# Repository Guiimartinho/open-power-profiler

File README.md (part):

# Open Power Profiler

[![Checks: run on demand][badge-checks]](CONTRIBUTING.md#quality-gates)
[![Status: early development][badge-status]](#roadmap)
[![Software license: MIT][badge-mit]](LICENSE)
[![Hardware license: CERN-OHL-P v2][badge-ohl]](hardware/LICENSE)

Open-source power profiler in the class of the Nordic PPK2, built around the
Raspberry Pi Pico 2. It is designed to sample current at 100 kSPS from
100 nA to 1 A with automatic range switching, to work either as a source
meter that powers the device under test or as an ampere meter in series
with an external supply, and to stream the samples to a PC over USB.

The instrument is two boards: a Raspberry Pi Pico 2, bought ready-made,
plugged into a carrier board designed in this project that holds the
measurement electronics.

The picture is a rendering from the KiCad files of draft A2, with the
Pico 2 on its sockets. It is not a photograph: no board has been built.

> [!NOTE]
> The project is in early development. No hardware has been built and
> nothing has been measured. The performance figures in this repository
> are design targets, the circuits of the board are simulated from its
> netlist, and the figures of the board are calculated from the drawn
> copper. [Project Status](#project-status) says what exists, what it
> rests on and what comes next.

## Table of Contents

- [Project Status](#project-status)
- [Target Specifications](#target-specifications)
- [How It Works](#how-it-works)
- [Connections](#connections)
- [Hardware Draft](#hardware-draft)
- [Circuit Simulations](#circuit-simulations)
- [Repository Structure](#repository-structure)
- [Roadmap](#roadmap)
- [Getting Started](#getting-started)
- [Engineering Practices](#engineering-practices)
- [Documentation](#documentation)
- [Contributing](#contributing)
- [License](#license)
- [Acknowledgments](#acknowledgments)

## Project Status

As of 2026-10-13. Draft A2 of the carrier board is the present state of
the hardware: the whole schematic, a specification written for it, and a
board with every part placed and every one of its 984 connections drawn.
The board was first routed by an autorouter, which left 28 connections
open. Its layout has since been reviewed: the open connections are closed
and the copper that an autorouter does not draw is drawn, the pours of the
1 A path, the guard, the sense pairs and the copper of the converters. The
review was done with scripts and checked by independent calculation. The
seven points where the reviewed board departs from the first wording of
section 10 of the specification are recorded decisions, D-87 to D-93, and
the specification follows them.

On 2026-10-13 a person looked at the drawings for the first time: the
project owner opened the schematic and the board in the KiCad editor and
found both coherent. It was a look, not a review item by item, and no
edit was saved. The same day the footprints and the placement were
reviewed on a copy of the project, with scripts on the board file, 3D
renderings of every region of the board and the datasheets. Five findings
of that review were worked into the board at single points, with no new
routing, and the silkscreen got the frames and names of the functional
blocks
([Review of Footprints and Placement](#review-of-footprints-and-placement)).
What is open is the review of the board item by item in the KiCad
editor, a list of items that need parts moved, what the silkscreen and
the test points still lack, and the thermal check of D-93.
Every figure of the board is calculated from the drawn copper, none is
measured; the package in [`tools/board/`](tools/board/README.md)
reproduces them from the board file.

Later on 2026-10-13 the project owner asked for the files that are needed
to send the board to fabrication. The fabrication outputs of draft A2 are
filed in
[`hardware/fabrication/draft-a2/`](hardware/fabrication/draft-a2/README.md)
for an order of proof-of-concept boards: eleven Gerber files of the
four-layer board, two drill files and two files for machine assembly.
That is decision D-105 of the specification. The items that the
specification puts before an order are still open, boards made from
these files are draft A2 and not revision A, and those items stay open.
No order is recorded: no board has been ordered or made as far as the
repository shows.

On 2026-10-10 the circuits of the schematic were simulated as well, block
by block, from its netlist: 134 benches in ngspice, of which 93 run
circuits of the board and 41 put the models into the test circuits of
their datasheets. The central design figures of the specification come
out again. The simulations raised four points for a decision before
boards are ordered, and the project owner decided them the same day: they
are decisions D-95 to D-98 of the specification. Three of them are drawn
since that day, as changes of values, part numbers and texts that move no
copper: 10 nF at three capacitors of the rail monitor (D-95), the two
parts of the damper on the module input fitted (D-98), and the text of
the detector position at the boost converter, which stays without a part
(D-97). The schematic, the board, the bill of materials and the netlist
snapshot of the simulations hold them, and the electrical rules check and
the design rules check report nothing on these files (run again on
2026-10-13).
The fourth is not drawn: a position for a capacitor at the buffer of the
driver rail (D-96), which needs a footprint and copper. The simulations
were not run again, so their results are still those of the circuit
before the three changes.

In fourteen places the simulations differed from a figure or a rule of
the specification or showed something that it did not state. The owner
asked for the text to follow the simulations: twelve places are corrected
in the specification, three of them by decisions D-99 to D-101, two wait
for the run of the benches on the drawn decisions, and seven questions
that the corrections leave are open, each with one recommendation. A
simulation is not a measurement: every active part in it is a model
written from a datasheet, a typical part at room temperature.
[Circuit Simulations](#circuit-simulations) shows the state.

The software is written ahead of the hardware and is tested without it.
Its state is that of 2026-10-12. On that day the firmware got a design of
its own, one level below the specification; the host protocol went to
version 2, which holds what draft A2 reports (D-103); and the firmware
directory became a project of the Pico SDK that builds an image for the
Pico 2. That image starts a console and the device state machine and
nothing more, and it has not been loaded onto a board: nothing has run on
a controller.

| Area | What exists | What is open |
| --- | --- | --- |
| [Specification](docs/specification.md) | The baseline of draft A2: requirements R-01 to R-17, analog and firmware design, pin map, host protocol, 105 recorded decisions and 36 firmware rules that guard hardware. D-95 to D-98 are the decisions of the project owner on the four points that the simulations raised, D-99 to D-101 are the three corrections of the text that change a rule, a test or advice to the user, and D-102 settles the license of the simulation folder. D-103 and D-104 are the decisions of 2026-10-12 on the software: version 2 of the host protocol, and the over-current trip as a program of its own in PIO 2. D-105 is the decision of 2026-10-13 on the first order: the fabrication outputs of draft A2 are filed for proof-of-concept boards while the items that precede an order are open | Every figure is a datasheet value, a calculation, a simulation or an estimate; the tests of its section 11 have to confirm them. The items of its section 16 under "Before the board is ordered" stay open after D-105 and remain conditions of revision A. Of the four decisions D-95 to D-98, three are drawn since 2026-10-10; the fourth, a position for a capacitor at the buffer of the driver rail (D-96), is stated here and not drawn. Of the fourteen other places where the simulations of 2026-10-10 differed from its text, twelve are corrected; two wait for the new run of the benches, and seven questions that the corrections leave are open in its section 16 |
| [Schematic](hardware/doc/README.md) | 428 parts on 15 pages. Three decisions that follow the simulations are drawn in it since 2026-10-10: 10 nF in place of 1 nF at three capacitors of the rail monitor (D-95), the two parts of the damper on the module input fitted (D-98), and the text of the detector position at the boost converter, which stays without a part (D-97). It passes the electrical rules check, run again on 2026-10-13. Before these three changes the netlist of the draft was checked independently against the datasheets, and its circuits were simulated from it. On 2026-10-13 its symbols were compared with the libraries and the datasheets: 55 of the 59 symbols of the parts are unchanged symbols of the KiCad library, and the four symbols of the project agree pin by pin with their datasheets. One field changed that day and no connection: the pre-regulator names a new project footprint | The [component checks](docs/checks/README.md): none is closed, so every part is a candidate; the comparison of 2026-10-13 closes none. One decision that follows the simulations is not drawn: a position for a capacitor at the buffer of the driver rail (D-96). The circuits that the three drawn changes touch have not been simulated again |
| [Board](hardware/README.md#board) | 150 mm × 100 mm, four layers, 425 footprints, 984 of 984 connections drawn, no violation in the design rules check, run again on 2026-10-13. The layout was reviewed on 2026-10-10 with scripts and checked by independent calculation. The three decisions drawn that day changed fields of six footprints (values, part numbers, fitted flags and one text) and no copper. On 2026-10-13 the project owner opened the project in the KiCad editor and found the schematic and the board coherent, and the footprints and the placement were reviewed with scripts on the board file, 3D renderings and the datasheets: every footprint equals its library footprint, no courtyard overlaps another, and nothing stands under the module. Five findings of that review are worked into the board: the pre-regulator stands on the land pattern of its own package, nine vias were moved away from pads and two from under the wall of the shield can, the reference texts stand at their own parts, and the console header has its pin names. The silkscreen carries the frames and names of the sixteen functional blocks. Calculated from the drawn copper, again after that round and unchanged: the 1 A path is 19.5 squares in source meter mode and 23.3 squares in ampere meter mode against a limit of 30, and the surface leakage into the measured node is 5.1 nA against a budget of 10 nA. The seven points where the layout departs from the first wording of section 10 of the specification are recorded as decisions D-87 to D-93 | No person has reviewed the board item by item in the KiCad editor: the owner's look of 2026-10-13 was not that review, and the review of footprints and placement was made outside the editor. Open items need parts moved, the capacitor loops of the converters among them. On the silkscreen 95 of the 425 reference texts are hidden, and the net names of the test points, the functions of the two jumpers and a frame for the serial number are missing; probe grounds at the test points are missing too. Two vias still stand at a pad, the lower edge of the frame of the shield can is not confirmed in a drawing of its maker, and the finger lands of the pre-regulator are not drawn. The temperature rise of the linear regulator is an open check, read on the first board (D-93). The position for a capacitor of D-96 is not on the board yet: it adds one footprint |
| [Bill of materials](hardware/doc/bom.csv) | 151 lines for 370 parts, each line with a part number and a maker, exported from the schematic on 2026-10-10 with the drawn decisions: the three capacitors of the rail monitor at 10 nF (D-95) and the two parts of the damper on the module input (D-98). Exported again on 2026-10-13: one line changed, the footprint of the pre-regulator | Three lines had no stock on 2026-10-09, among them the capacitor that the damper uses. One position stays without a part and is not in the file: the detector position at the boost converter (D-97) |
| [Fabrication outputs](hardware/fabrication/draft-a2/README.md) | Filed on 2026-10-13 for an order of proof-of-concept boards of draft A2, by decision D-105 of the project owner: eleven Gerber files of the four-layer board and two drill files, also as one archive, and two files for machine assembly with the 360 surface-mount placements of the top side in 142 lines. They were exported from the board file with `kicad-cli`. Two things were checked on them: the drill file holds 787 plated holes, which are the 694 vias and the 93 holes of pads of the board, and every layer, the drill file and the placement file lie in one coordinate frame | No order is recorded: no board has been ordered or made as far as the repository shows. No Gerber viewer has read the files back, and no manufacturer has reviewed them. The assembly files carry manufacturer part numbers only, and their rotations are those of KiCad. The order is the project owner's; it still needs the surface finish ENIG in the order form, a word on the mark of the order number, the rotations checked in the preview of the assembler, and the parts matched by their manufacturer part numbers. Boards made from these files are draft A2, not revision A |
| [Circuit simulations](simulation/README.md) | The circuits of draft A2 simulated in ngspice on 2026-10-10 from the netlist of the schematic as it stood that day, before the three decisions were drawn, in a package of their own (D-94): 134 benches, 93 on the circuits of the board in ten blocks and 41 that put the models written for the project into the test circuits of their datasheets. Of 3162 figures 1834 pass, 122 fail and 1206 carry no limit. The central design figures of the specification come out again block by block: shunt ladder, signal chain, range logic with requirement R-07, source meter, output stage, path switches, rails, power input and digital lines. The package has 777 tests; lines and branches are covered in full, the one module that loads the simulator excepted; its gates passed again on 2026-10-12 | The four points that the simulations raised are decided (D-95 to D-98): the capacitors of the rail monitor, the buffer of the driver rail, the detector position at the boost converter and the damper on the module input. Three of them are drawn since 2026-10-10 and are in the netlist snapshot of the package (D-95, D-97, D-98); the snapshot still matches the schematic on 2026-10-13. The results are still those of the run of 2026-10-10, on the circuit before these changes: the benches were not run again, and those of the power input still leave the two parts of the damper out. Open work: the benches brought in line with the snapshot, and the blocks that the changes touch run again, the rail monitor with the power-up and the power-off and the input from the module. In fourteen places the simulation and the text of the specification differed: twelve are corrected in the specification, two wait for the new run, and seven questions are open. The limits of the benches are still those of the earlier text. What stays for the bench: leakage at the nanoampere level, the multiplexer at +12 V and −4 V, the programs of the controller, coupling through the board, temperature. Every active part is a model written from its datasheet, and nothing is measured. The simulations ran on one machine; the `Simulation` workflow has not been started yet |
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
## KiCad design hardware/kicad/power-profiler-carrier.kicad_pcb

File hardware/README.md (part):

# Hardware

The carrier board of the instrument: schematic, PCB layout and fabrication
outputs. The simulations of its circuits are a package of their own, in
[`../simulation/`](../simulation/README.md).

The instrument is two boards. A Raspberry Pi Pico 2, bought ready-made, is
the controller. It plugs into two rows of pin sockets on the carrier board
designed here, which holds everything else: power input, source meter, shunt
ladder, signal chain, side data and connectors. Sections 4.11 and 5 of the
[specification](../docs/specification.md) define the interface.

The picture is a rendering from the KiCad files, with the Pico 2 on its
sockets. It is not a photograph: no board has been built.

## Status

Draft A2 with a reviewed layout, as of 2026-10-13. The KiCad project holds
the whole carrier board: the schematic with 428 parts on fifteen A4 pages
(the root sheet and fourteen sheets) and a four-layer board of
150 mm × 100 mm on which every connection is drawn. The board was placed by
a script and routed by an autorouter, which left 28 connections open. On
2026-10-10 its layout was reviewed with scripts: the open connections were
closed and the copper that an autorouter does not draw was drawn. Every
figure of the board in this guide is calculated from the drawn copper. On
the same day the circuits of the schematic were simulated from its netlist,
block by block; the central design figures of the specification come out
again ([Circuit Simulations](#circuit-simulations)). The simulations
raised four points, which the owner decided the same day: decisions D-95
to D-98 of the specification. Three of them are drawn since that day, as
changes of values, part numbers, fitted flags and texts: 10 nF at C32 to
C34 (D-95), the damper R14 and C5 fitted (D-98), and the text of the
position U9, which stays without a part (D-97). They changed no copper and
moved no part. The fourth is not drawn: a position for a capacitor at the
buffer U28 (D-96), which needs a footprint and copper. The simulations
were not run again, so their results describe the circuit before the
three changes
([Decisions That Follow the Simulations](#decisions-that-follow-the-simulations)).

On 2026-10-13 the owner opened the project in the KiCad editor, the
schematic and the board, and found both coherent. That was a look, not a
review item by item, and no edit was saved. The same day the footprints
and the placement were reviewed on a copy of the project, with scripts on
the board file, 3D renderings of every region of the board and the
datasheets. Five findings of that review were worked into the board, at
those points only and with no new routing: the pre-regulator U16 has the
land pattern of its own package, eleven vias were moved away from pads and
from under the wall of the shield can, reference texts stand at their own
parts, and the console header J1 has the names of its pins. The silkscreen
also carries the frames and names of the sixteen functional blocks now
([Review of Footprints and Placement](#review-of-footprints-and-placement-2026-10-13)).
Both rule checks report nothing on the present files (run on 2026-10-13).
Nobody has reviewed the board item by item in the KiCad editor, no board
is built, and nothing is measured.

Later that day the owner asked for the files that are needed to send the
board to fabrication. The fabrication outputs of draft A2 are filed in
[`fabrication/draft-a2/`](fabrication/draft-a2/README.md) for an order of
proof-of-concept boards. That is decision D-105 of the specification: the
items that the specification puts before an order are still open, boards
made from these files are draft A2 and not revision A, and those items
stay open
([Fabrication Outputs of Draft A2](#fabrication-outputs-of-draft-a2)).
No order is recorded: no board has been ordered or made as far as the
repository shows.

| What | State |
| --- | --- |
| Schematic | Every sheet drawn: 428 parts, 225 nets, 15 pages; not changed by the layout review. Three decisions of 2026-10-10 are drawn in it since that day, as changes of values, part numbers, fitted flags and texts: 10 nF at C32 to C34 (D-95), R14 and C5 fitted (D-98), the text of the position U9 (D-97). One is not drawn: the position for a capacitor at U28 (D-96). On 2026-10-13 one field changed and no connection: U16 on the Source Meter sheet, and its symbol in the project library, name the new project footprint |
| Electrical rules check | 0 errors, 0 warnings; run again on 2026-10-13, after the round that followed the review of footprints and placement |
| Netlist against datasheets | Checked independently, before the three decisions were drawn; no blocker and no major defect found |
| Symbols and footprints against libraries and datasheets | Compared on 2026-10-13: every footprint of the board equals its library footprint pad by pad, 55 of the 59 symbols of the parts are unchanged symbols of the KiCad library, and the four project symbols agree pin by pin with their datasheets ([list](#what-was-compared)). It closes no component check |
| Bill of materials | 151 lines for 370 parts, each line with a part number and a maker; three lines without stock on 2026-10-09; not changed by the layout review. Exported again on 2026-10-10: it holds 10 nF at C32 to C34 (D-95) and the two parts of the damper, R14 and C5 (D-98). Exported again on 2026-10-13: one line changed, the footprint of U16 |
| Component checks | 0 closed; every part is a candidate |
| Board, placement | 425 footprints placed by a script, all on the top side; 35 of them moved or turned in the layout review, none since. Reviewed on 2026-10-13 with scripts on the board file, 3D renderings and datasheets: no courtyard overlaps another, nothing stands under the module, 58 parts stand inside the shield can and none across its wall ([list](#what-was-compared)). Not reviewed item by item by a person in the KiCad editor |
| Board, routing | 984 of 984 connections, none open: 8.40 m of track in 3,743 segments, 694 vias, 42 copper zones. The round of 2026-10-13 routed nothing again: it moved eleven vias and added 27 short pieces of track, 15.9 mm in all, to the 3,716 segments that the board had (8.38 m), which are unchanged |
| Design rules check with schematic parity | 0 violations, 0 unconnected pads, 0 footprint errors, 0 differences between board and schematic, against a rule file that asks more than the one of the autorouted board; run again on 2026-10-13, after the round of that day |
| Layout review | Done on 2026-10-10 with scripts and checked by independent calculation |
| Look in the KiCad editor | On 2026-10-13 the owner opened the schematic and the board in the KiCad editor and found both coherent. A look, not a recorded review item by item; no edit was saved |
| Review of footprints and placement | Done on 2026-10-13 on a copy of the project, with scripts on the board file, 3D renderings of every region of the board and the datasheets. Five findings, each worked into the board the same day ([section](#review-of-footprints-and-placement-2026-10-13)) |
| Silkscreen | Since 2026-10-13: the frames and names of the sixteen functional blocks, the pin names of the console header J1, and 330 of the 425 reference texts visible, each at its own part; 95 are hidden, and every hidden reference is on the fabrication layer. Missing: the net names of the test points, the functions of the two jumpers and a frame for the serial number |
| 1 A path, copper only | 19.5 squares (10.4 mΩ at 40 °C) in source mode and 23.3 squares (12.3 mΩ at 40 °C) in ampere mode, against a limit of 30 squares; calculated from the drawn copper, again on 2026-10-13 with the same result |
| Surface leakage into the measured node | 5.1 nA against a budget of 10 nA; calculated from the drawn copper with the assumptions of section 10.3 of the specification, again on 2026-10-13 with the same result |
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
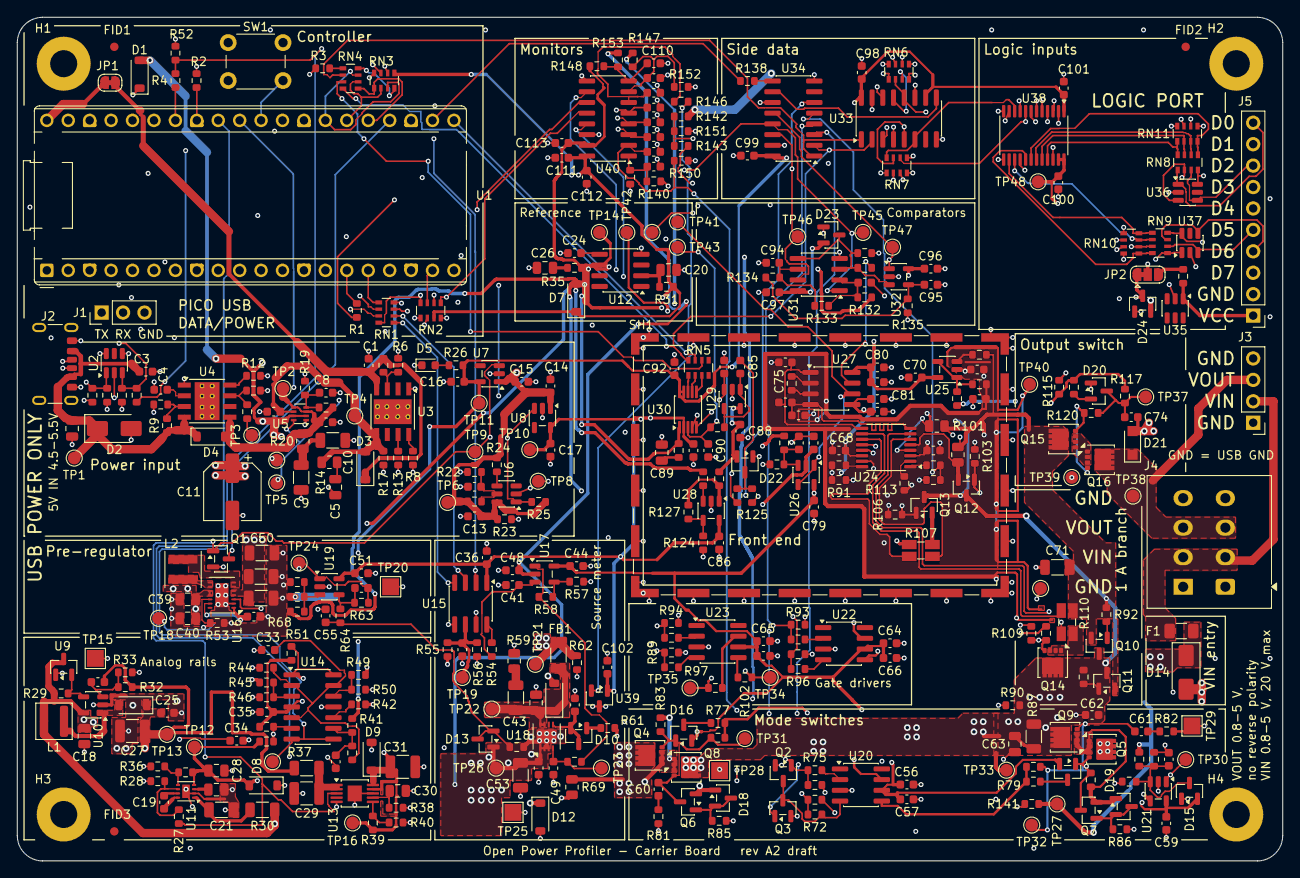
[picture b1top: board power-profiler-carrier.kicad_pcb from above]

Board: 4 copper layers, 150.0 x 100.0 mm, 425 parts (0 on the bottom side), 225 nets.

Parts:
C1, C3, C13, C25, C35, C36, C37, C38, C44, C48, C49, C51, C54, C55, C57, C59, C60, C61, C66, C67, C68, C69, C70, C72, C73, C79, C80, C81, C84, C86, C88, C93, C94, C95, C96, C97, C98, C99, C100, C101, C102, C103, C104, C105, C106, C107, C108, C109, C110, C111, C113: 100n 50V X7R; C_0603_1608Metric
C2, C18, C20, C22, C28, C30, C63: 4.7u 25V X7R; C_0805_2012Metric
C4: 3.3n 50V X7R; C_0603_1608Metric
C5, C39, C40, C46: 10u 25V X5R; C_0805_2012Metric
C6, C7, C14, C15, C16, C17, C19, C24, C41, C47, C56, C62, C64, C65, C78, C82, C83, C91, C92, C112: 1u 25V X7R; C_0603_1608Metric
C8: 33n 50V X7R; C_0603_1608Metric
C9, C10, C21: 22u 10V X7R; C_1206_3216Metric
C11: 47u 16V; CP_Elec_6.3x5.4
C12, C58: 1n 50V C0G; C_0603_1608Metric
C23, C77: 220p 50V C0G; C_0603_1608Metric
C26: 10u 16V X7R; C_0805_2012Metric
C27, C29, C31: 10u 25V X7R; C_1210_3225Metric
C32, C33, C34, C74: 10n 50V C0G; C_0603_1608Metric
C42, C43, C45, C50, C53: 22u 25V X5R; C_1206_3216Metric
C52: 10p 50V C0G; C_0603_1608Metric
C71: 100n 50V C0G; C_1206_3216Metric
C75, C76: 22p 50V C0G; C_0603_1608Metric
C85: 1.5n 50V C0G; C_0603_1608Metric
C87: 680p 50V C0G; C_0603_1608Metric
C89: 22u 6.3V X5R; C_0805_2012Metric
C90: 10n 25V C0G; C_0603_1608Metric
D1, D3, D4, D11, D12: 1N5819HW; D_SOD-123
D2: SMAJ10A; D_SMA
D5: green 2.0V; LED_0603_1608Metric
D6, D7, D8, D9: B0530W 30V 0.5A; D_SOD-123
D10, D13, D15, D16, D17, D18, D19, D20, D22, D23: BAV199; SOT-23
D14: SMAJ20CA; D_SMA
D21: PTVS15VS1UR; Nexperia_CFP3_SOD-123W
D24: BAT54S; SOT-23
F1: 4A fast 32V; Fuse_1206_3216Metric
FB1: 50R 12A; L_1206_3216Metric
FID1, FID2, FID3: Fiducial; Fiducial_1mm_Mask2mm
H1, H2, H3, H4: M3; MountingHole_3.2mm_M3_Pad
J1: Debug UART; PinHeader_1x03_P2.54mm_Vertical
J2: USB-C power; USB_C_Receptacle_GCT_USB4125-xx-x_6P_TopMnt_Horizontal
J3: DUT; PinHeader_1x04_P2.54mm_Vertical
J4: DUT wires; TerminalBlock_WAGO_2601-1104_1x04_P3.50mm_Horizontal_Pad1.9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
J5: Logic port; PinHeader_1x10_P2.54mm_Vertical
JP1: USB of Pico feeds +5V; SolderJumper-2_P1.3mm_Bridged_RoundedPad1.0x1.5mm
JP2: VOUT / VCC pin; SolderJumper-3_P1.3mm_Bridged12_RoundedPad1.0x1.5mm
L1: 10u 3A; L_Wuerth_MAPI-4030
L2: 1.5u 4.6A; L_Coilcraft_XxL4020
Q1, Q2, Q3: BSS138; SOT-23
Q4, Q5, Q8, Q9, Q14, Q15, Q16: CSD17577Q3A; VSON-8_3.3x3.3mm_P0.65mm_NexFET
Q6, Q7: BC847B; SOT-23
Q10, Q11, Q12, Q13: IRLML0030; SOT-23
R1, R71: 4.7k 1%; R_0603_1608Metric
R2: 0R; R_0603_1608Metric
R3, R51: 1.5k 1%; R_0603_1608Metric
R4, R26, R53, R60, R62, R70, R72, R75, R88, R89, R93, R94, R96, R97, R98, R99, R111, R112, R118, R146: 1k 1%; R_0603_1608Metric
R5, R9: 4.53k 1%; R_0603_1608Metric
R6, R10: 3.01k 1%; R_0603_1608Metric
R7, R11, R91, R95: 5.1k 1%; R_0603_1608Metric
R8, R12: 402k 1%; R_0603_1608Metric
R13: 1.21k 1%; R_0603_1608Metric
R14, R20, R59: 0.33R 1%; R_0805_2012Metric
R15: 453R 1%; R_0603_1608Metric
R16, R19, R23, R25, R41, R54, R113, R114, R126, R144, R145, R150, R152: 10k 1%; R_0603_1608Metric
R17, R24, R27, R42, R50, R78, R80, R85, R86, R90, R103, R106, R109, R115, R148, R149, R151: 100k 1%; R_0603_1608Metric
R18: 13.7k 1%; R_0603_1608Metric
R21: 86.6k 0.1%; R_0603_1608Metric
R22, R57: 10k 0.1% 25ppm; R_0603_1608Metric
R28: 150k 1%; R_0603_1608Metric
R29: 51k 1%; R_0603_1608Metric
R30: 2.2R 1% 0.25W; R_1206_3216Metric
R31, R61, R108, R120, R129: 10R 1%; R_0603_1608Metric
R32: 133k 1%; R_0603_1608Metric
R33: 13.3k 1%; R_0603_1608Metric
R34: 226k 0.1%; R_0603_1608Metric
R35: 1R 1%; R_0603_1608Metric
R36, R67, R74: 100k 0.1% 25ppm; R_0603_1608Metric
R37: 0.47R 1% 0.25W; R_1206_3216Metric
R38: 120k 0.1%; R_0603_1608Metric
R39: 442k 1%; R_0603_1608Metric
R40: 12.4k 1%; R_0603_1608Metric
R43: 40.2k 1%; R_0603_1608Metric
R44, R46, R47: 49.9k 1%; R_0603_1608Metric
R45: 249k 1%; R_0603_1608Metric
R48: 127k 1%; R_0603_1608Metric
R49: 36.5k 1%; R_0603_1608Metric
R52, R81, R82: 6.8k 1%; R_0603_1608Metric
R55, R56: 2.00k 0.1% 25ppm; R_0603_1608Metric
R58, R124: 11k 0.1% 25ppm; R_0603_1608Metric
R63: 19.1k 0.1% 25ppm; R_0603_1608Metric
R64: 93.1k 0.1% 25ppm; R_0603_1608Metric
R65: 6.65k 0.1% 25ppm; R_0603_1608Metric
R66: 23.7k 0.1% 25ppm; R_0603_1608Metric
R68: 137k 0.1% 25ppm; R_0603_1608Metric
R69: 1.3k 1%; R_0805_2012Metric
R73: 115k 0.1%; R_0603_1608Metric
R76: 3.3M 1%; R_0603_1608Metric
R77, R79, R92, R100, R130: 22R 1%; R_0603_1608Metric
R83, R84, R117: 2.2M 1%; R_0603_1608Metric
R87: 0.47R 1% 0.5W; R_1206_3216Metric
R101: 1k 0.1% 25ppm; R_0805_2012Metric
R102, R105, R119: 47R 1%; R_0603_1608Metric
R104: 33R 0.1% 25ppm; R_0805_2012Metric
R107: 1R 0.5% 25ppm; R_Shunt_Ohmite_LVK12
R110: 0.1R 0.25% 50ppm; R_Shunt_Ohmite_LVK12
R116: 220R 1%; R_0603_1608Metric
R121: 49.9k 0.1% 25ppm; R_0603_1608Metric
R122: 1.02k 0.1% 25ppm; R_0603_1608Metric
R123: 523R 0.1% 25ppm; R_0603_1608Metric
R125, R128: 3.9k 1%; R_0603_1608Metric
R127, R137: 1k 0.1% 25ppm; R_0603_1608Metric
R131: 0.22R 1%; R_0603_1608Metric
R132: 34.8k 0.1% 25ppm; R_0603_1608Metric
R133: 3.6k 0.1% 25ppm; R_0603_1608Metric
R134: 2.4k 0.1% 25ppm; R_0603_1608Metric
R135: 9.31k 0.1% 25ppm; R_0603_1608Metric
R136: 3.01k 0.1% 25ppm; R_0603_1608Metric
R138: 33R 1%; R_0603_1608Metric
R139: 100R 1%; R_0603_1608Metric
R140, R142: 120k 1%; R_0603_1608Metric
R141: 430k 1%; R_0603_1608Metric
R143: 68.1k 1%; R_0603_1608Metric
R147: 47k 1%; R_0603_1608Metric
R153: 200k 1%; R_0603_1608Metric
RN1: 2.2k; R_Array_Convex_4x0603
RN2, RN3: 4.7k; R_Array_Convex_4x0603
RN4: 47R; R_Array_Convex_4x0603
RN5: 220R 5%; R_Array_Convex_4x0603
RN6, RN7: 100k; R_Array_Convex_4x0603
RN8, RN9: 330R; R_Array_Convex_4x0603
RN10, RN11: 470k; R_Array_Convex_4x0603
SH1: BMI-S-210-F; Laird_Technologies_BMI-S-210-F_44.00x30.50mm
SW1: RESET; SW_PUSH_6mm
TP1: VBUS_C; TestPoint_Pad_D1.5mm
TP2: VBUS_CP; TestPoint_Pad_D1.5mm
TP3: IMON; TestPoint_Pad_D1.5mm
TP4: VBUS_P; TestPoint_Pad_D1.5mm
TP5: SRC; TestPoint_Pad_D1.5mm
TP6: +5V; TestPoint_Pad_D1.5mm
TP7, TP8, TP39: GND; TestPoint_Pad_D1.5mm
TP9: 5V_OK; TestPoint_Pad_D1.5mm
TP10: +3V3_A; TestPoint_Pad_D1.5mm
TP11: +3V3_C; TestPoint_Pad_D1.5mm
TP12: -4V_A; TestPoint_Pad_D1.5mm
TP13: +13V5; TestPoint_Pad_D1.5mm
TP14: VREF; TestPoint_Pad_D1.5mm
TP15, TP20, TP25, TP28, TP29: GND; TestPoint_Pad_2.0x2.0mm
TP16: +12V_A; TestPoint_Pad_D1.5mm
TP17: PWR_GOOD; TestPoint_Pad_D1.5mm
TP18: SMU_EN; TestPoint_Pad_D1.5mm
TP19: VREF_DAC; TestPoint_Pad_D1.5mm
TP21: V_PRE; TestPoint_Pad_D1.5mm
TP22: LDO_IN; TestPoint_Pad_D1.5mm
TP23: LDO_SET; TestPoint_Pad_D1.5mm
TP24: PRE_FB; TestPoint_Pad_D1.5mm
TP26: LDO_OUT; TestPoint_Pad_D1.5mm
TP27: VIN_P; TestPoint_Pad_D1.5mm
TP30: VIN_OV; TestPoint_Pad_D1.5mm
TP31: SRC_G; TestPoint_Pad_D1.5mm
TP32: AMP_G; TestPoint_Pad_D1.5mm
TP33: SUPPLY; TestPoint_Pad_D1.5mm
TP34: G_R1; TestPoint_Pad_D1.5mm
TP35: G_R2; TestPoint_Pad_D1.5mm
TP36: G_R3; TestPoint_Pad_D1.5mm
TP37: OUT_GATE; TestPoint_Pad_D1.5mm
TP38: VOUT; TestPoint_Pad_D1.5mm
TP40: GUARD; TestPoint_Pad_D1.5mm
TP41: PED; TestPoint_Pad_D1.5mm
TP42: VDRV; TestPoint_Pad_D1.5mm
TP43: ADC_IN; TestPoint_Pad_D1.5mm
TP44: AMP_RAW; TestPoint_Pad_D1.5mm
TP45: CMP_JUMP; TestPoint_Pad_D1.5mm
TP46: CMP_OC; TestPoint_Pad_D1.5mm
TP47: CMP_UP; TestPoint_Pad_D1.5mm
TP48: VCC_B; TestPoint_Pad_D1.5mm
U1: Raspberry Pi Pico 2; RaspberryPi_Pico_Common_THT_NoKeepout
U2, U35, U36, U37: TPD4E1U06DBVR; SOT-23-6
U3, U4: TPS259621DDAR; TI_SO-PowerPAD-8_ThermalVias
U5: TPS2116DRLR; SOT-583-8
U6: TPS3808G01DBVR; SOT-23-6
U7, U8: LP5907MFX-3.3; SOT-23-5
U9: Detector, ms time-out; SOT-23
U10: LMR62014XMF; SOT-23-5
U11: LM27761DSG; WSON-8-1EP_2x2mm_P0.5mm_EP0.9x1.6mm
U12: REF5025AID; SOIC-8_3.9x4.9mm_P1.27mm
U13: LT3042EMSE; MSOP-10-1EP_3x3mm_P0.5mm_EP1.68x1.88mm
U14: MCP6569-E/SL; SOIC-14_3.9x8.7mm_P1.27mm
U15: MCP4921-E/SN; SOIC-8_3.9x4.9mm_P1.27mm
U16: TPS63020DSJ; Texas_R-PVSON-N14_3x4mm_P0.5mm_EP1.58x2.85mm
U17, U25, U26: OPA197IDBV; SOT-23-5
U18: LT3080EDD; DFN-8-1EP_3x3mm_P0.5mm_EP1.66x2.38mm
U19, U28, U29: OPA365AIDBV; SOT-23-5
U20, U22, U23: TC4427EOA; SOIC-8_3.9x4.9mm_P1.27mm
U21, U32: MCP6561T-E/OT; SOT-23-5
U24: MUX509IPWR; TSSOP-16_4.4x5mm_P0.65mm
U27: AD8421ARZ; SOIC-8_3.9x4.9mm_P1.27mm
U30: ADS8860IDGS; MSOP-10_3x3mm_P0.5mm
U31: MCP6562-E/SN; SOIC-8_3.9x4.9mm_P1.27mm
U33, U34: SN74LV165ADR; SOIC-16_3.9x9.9mm_P1.27mm
U38: SN74LVC8T245PW; TSSOP-24_4.4x7.8mm_P0.65mm
U39: MCP9700AT-E/TT; SOT-23
U40: MCP3208-BI/SL; SOIC-16_3.9x9.9mm_P1.27mm

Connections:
+3V3_A: C17.1, C36.1, C51.1, C59.1, C86.1, C91.1, C96.1, C97.1, C102.1, C111.1, C112.1, D7.1 (K), D15.2 (K), D23.2 (K), R31.1, R42.1, RN2.7 (R2.2), RN3.5 (R4.2), TP10.1 (1_1), U8.5 (OUT), U15.1 (Vdd), U19.5 (V+), U21.5 (V+), U28.5 (V+), U30.2 (AVDD), U31.8 (V+), U32.5 (V+), U39.1 (V_{DD}), U40.16 (Vdd)
+3V3_C: C16.1, C35.1, C92.1, C98.1, C99.1, C101.1, R26.1, R41.1, R47.1, R51.1, TP11.1 (1_1), U7.5 (OUT), U14.4 (V+), U30.9 (DIN), U30.10 (DVDD), U33.10 (DS), U33.16 (VCC), U34.16 (VCC), U38.1 (V_{CCA})
+5V: C11.1, C13.1, C14.1, C15.1, C18.1, C39.1, C40.1, D1.2 (A), D24.2 (K), L1.1, R21.1, R23.1, R24.1, R25.1, R29.1, R30.1, R142.1, TP6.1 (1_1), U5.2 (VOUT), U5.7 (VOUT), U6.6 (VDD), U7.1 (IN), U8.1 (IN), U9.3 (V_{DD}), U10.5 (VIN), U16.10 (VIN), U16.11 (VIN)
+12V_A: C31.1, C44.1, C56.1, C57.1, C64.1, C65.1, C66.1, C67.1, C68.1, C70.1, C79.1, C80.1, C83.1, D9.1 (K), D16.2 (K), D17.2 (K), R39.1, R45.1, R113.1, R147.1, TP16.1 (1_1), U13.9 (OUTS), U13.10 (OUT), U17.5 (V+), U20.6 (V_{DD}), U22.6 (V_{DD}), U23.6 (V_{DD}), U24.14 (VDD), U25.5 (V+), U26.5 (V+), U27.8 (Vs+)
+13V5: C23.1, C25.1, C27.1, D6.1 (K), R32.1, R37.1, R61.1, TP13.1 (1_1)
-4V_A: C28.2, C48.2, C69.2, C72.2, C81.2, C82.2, C84.2, D8.2 (A), R34.2, R48.2, R69.2, R153.2, TP12.1 (1_1), U11.4 (VOUT), U17.2 (V-), U24.3 (VSS), U25.2 (V-), U26.2 (V-), U27.5 (Vs-)
/Analog Rails/5V_OK: Q1.1 (G), R25.2, R27.1, TP9.1 (1_1), U6.1 (~RESET), U7.3 (EN), U8.3 (EN), U13.3 (EN/UV)
/Comparators/AMP_RAW: R125.1, R136.1, TP44.1 (1_1), U27.7
/Comparators/CMP_JUMP: TP45.1 (1_1), U1.12 (GPIO9), U31.1, U34.13 (D2)
/Comparators/CMP_OC: TP46.1 (1_1), U1.14 (GPIO10), U31.7, U34.14 (D3)
/Comparators/CMP_UP: TP47.1 (1_1), U1.11 (GPIO8), U32.1, U34.12 (D1)
/Controller/ADC_CNV: RN4.7 (R2.2), RN5.6 (R3.2)
/Controller/ADC_DOUT: RN5.7 (R2.2), U1.21 (GPIO16)
/Controller/ADC_SCK: RN4.8 (R1.2), RN5.8 (R1.2), U33.2 (CP), U34.2 (CP)
/Controller/C_DAC_CS: R3.2, U15.2 (~CS)
/Controller/C_MISO: RN1.8 (R1.2), RN2.1 (R1.1), U40.12 (Dout)
/Controller/C_MON_CS: RN1.7 (R2.2), U40.10 (~CS/SHDN)
/Controller/C_MOSI: RN1.5 (R4.2), U15.4 (SDI), U40.11 (Din)
/Controller/C_SCK: RN1.6 (R3.2), U15.3 (SCK), U40.13 (CLK)
/Controller/GATE_AMP: R71.1, R72.1, U1.32 (GPIO27_ADC1)
/Controller/GATE_OUT: R93.1, R98.1, U1.10 (GPIO7), U34.4 (D5)
/Controller/GATE_R1: R89.1, R97.1, U1.4 (GPIO2)
/Controller/GATE_R2: R94.1, R99.1, U1.5 (GPIO3)
/Controller/GATE_R3: R88.1, R96.1, U1.6 (GPIO4)
/Controller/GATE_SRC: Q2.1 (G), R70.1, R75.1, U1.31 (GPIO26_ADC0)
/Controller/MUX_A0: R95.1, R112.1, U1.7 (GPIO5), U34.5 (D6)
/Controller/MUX_A1: R91.1, R111.1, U1.9 (GPIO6), U34.6 (D7)
/Controller/PICO_5V: C1.1, D3.1 (K), JP1.2 (B), R5.1, U3.4 (VIN)
/Controller/PWR_GOOD: R4.1, R51.2, R52.1, TP17.1 (1_1), U14.1, U14.7, U14.8, U14.14, U34.11 (D0)
/Controller/SIDE_DOUT: R138.2, U1.22 (GPIO17)
/Controller/SIDE_LOAD: RN4.6 (R3.2), U33.1 (~PL), U34.1 (~PL)
/Controller/SMU_ON: Q1.3 (D), U1.24 (GPIO18)
/Controller/VIN_OV: Q3.1 (G), R1.1, R76.2, TP30.1 (1_1), U21.1, U34.3 (D4)
/Digital Inputs/DIN0: RN6.1 (R1.1), U33.11 (D0), U38.3 (A1)
/Digital Inputs/DIN1: RN6.2 (R2.1), U33.12 (D1), U38.4 (A2)
/Digital Inputs/DIN2: RN6.3 (R3.1), U33.13 (D2), U38.5 (A3)
/Digital Inputs/DIN3: RN6.4 (R4.1), U33.14 (D3), U38.6 (A4)
/Digital Inputs/DIN4: RN7.1 (R1.1), U33.3 (D4), U38.7 (A5)
/Digital Inputs/DIN5: RN7.2 (R2.1), U33.4 (D5), U38.8 (A6)
/Digital Inputs/DIN6: RN7.3 (R3.1), U33.5 (D6), U38.9 (A7)
/Digital Inputs/DIN7: RN7.4 (R4.1), U33.6 (D7), U38.10 (A8)
/Digital Inputs/VCCB_SRC: D24.3 (COM), JP2.1 (A), R118.2
/Monitors/CC1: J2.A5 (CC1), R7.1, R144.1, U2.1 (IO1)
/Monitors/CC2: J2.B5 (CC2), R11.1, R145.1, U2.3 (IO2)
/Monitors/SRC_ST: R143.2, TP5.1 (1_1), U5.8 (ST)
/Monitors/VIN_P: D14.1 (A1), F1.2, Q5.5 (D), R73.1, R141.1, TP27.1 (1_1)
/Monitors/VOUT_BUF: C73.1, R119.2, R140.1, TP40.1 (1_1)
/Output Stage/DRV_OUT: R115.1, R116.1, R117.1, U22.7 (OUT_A)
/Output Stage/VIN_RAW: F1.1, J3.2, J4.2
/Output Stage/VOUT_S: C71.1, Q10.2 (S), Q11.2 (S), Q15.5 (D), R101.2, R104.2, R107.4, R110.4, R114.1, U24.12 (S2B), U24.13 (S1B)
/Path Switching/LDO_OUT: C53.1, C54.1, D11.2 (A), D12.1 (K), D13.1 (A), Q4.5 (D), R65.1, R69.1, TP26.1 (1_1), U18.1 (OUT), U18.2 (OUT), U18.3 (OUT), U18.9 (OUT)
/Path Switching/SUPPLY: C62.1, Q8.5 (D), Q9.5 (D), Q10.3 (D), Q11.3 (D), Q12.3 (D), Q13.3 (D), Q14.5 (D), R87.1, R90.1, R92.1, R100.1, R101.1, TP33.1 (1_1), U24.4 (S1A)
/Shunt Ladder/INN: C75.1, C77.2, U24.9 (DB), U27.1 (-)
/Shunt Ladder/INP: C76.1, C77.1, U24.8 (DA), U27.4 (+)
GND: C1.2, C2.2, C3.2, C4.2, C5.2, C6.2, C7.2, C8.2, C9.2, C10.2, C11.2, C12.2, C13.2, C14.2, C15.2, C16.2, C17.2, C18.2, C20.2, C21.2, C22.1, C24.2, C25.2, C26.2, C27.2, C28.1, C29.2, C30.2, C31.2, C32.2, C33.2, C34.2, C35.2, C36.2, C37.2, C38.2, C39.2, C40.2, C41.2, C42.2, C44.2, C45.2, C46.2, C47.2, C48.1, C49.2, C50.2, C51.2, C53.2, C54.2, C55.2, C56.2, C57.2, C58.2, C59.2, C62.2, C63.2, C64.2, C65.2, C66.2, C67.2, C68.2, C69.1, C70.2, C71.2, C72.1, C73.2, C74.2, C75.2, C76.2, C78.2, C79.2, C80.2, C81.1, C82.1, C83.2, C84.1, C86.2, C87.2, C88.2, C89.2, C90.2, C91.2, C92.2, C93.2, C94.2, C95.2, C96.2, C97.2, C98.2, C99.2, C100.2, C101.2, C102.2, C103.2, C104.2, C105.2, C106.2, C107.2, C108.2, C109.2, C110.2, C111.2, C112.2, C113.2, D2.2 (A2), D5.1 (K), D8.1 (K), D9.2 (A), D12.2 (A), D14.2 (A2), D15.1 (A), D20.1 (A), D21.2 (A), D22.1 (A), D23.1 (A), D24.1 (A), H1.1 (1_1), H2.1 (1_1), H3.1 (1_1), H4.1 (1_1), J1.3, J2.A12 (GND)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
unnamed: C5.1, R14.2
unnamed: C9.1, C10.1, R20.2
unnamed: C26.1, R35.2
unnamed: C29.1, R37.2, U13.1 (IN), U13.2 (IN)
unnamed: C42.1, C45.1, C50.1, FB1.1, R62.1, R67.1, TP21.1 (1_1), U16.4 (VOUT), U16.5 (VOUT)
unnamed: C43.2, R59.1
unnamed: C60.2, R81.1
unnamed: C61.2, R82.1
unnamed: C63.1, R87.2
unnamed: C89.1, R131.2
unnamed: D1.1 (K), U1.39 (VSYS)
unnamed: C2.1, C3.1, D2.1 (A1), D4.1 (K), J2.A9 (VBUS), J2.B9 (VBUS), R9.1, TP1.1 (1_1), U4.4 (VIN)
unnamed: C6.1, D3.2 (A), R14.1, R17.1, TP4.1 (1_1), U3.5 (OUT), U5.6 (VIN2)
unnamed: C7.1, D4.2 (A), R18.1, R20.1, TP2.1 (1_1), U4.5 (OUT), U5.3 (VIN1), U5.5 (MODE)
unnamed: D5.2 (A), R26.2
unnamed: D6.2 (A), L1.2, U10.1 (SW)
unnamed: D10.1 (A), R61.2
unnamed: C47.1, D10.2 (K), D10.3 (common), U18.5 (V_{CONTROL})
unnamed: C43.1, C46.1, D11.1 (K), FB1.2, TP22.1 (1_1), U18.7 (IN), U18.8 (IN)
unnamed: C55.1, D13.2 (K), D13.3 (common), R64.1, R65.2
unnamed: C58.1, D15.3 (common), R73.2, R74.1, R76.1, U21.3 (+)
unnamed: C60.1, D16.1 (A), Q4.4 (G), Q6.3 (C), Q8.4 (G), R78.2, R83.1, TP31.1 (1_1)
unnamed: D16.3 (common), R77.2
unnamed: C61.1, D17.1 (A), Q5.4 (G), Q7.3 (C), Q9.4 (G), R80.2, R84.1, TP32.1 (1_1)
unnamed: D17.3 (common), R79.2
unnamed: D18.1 (A), Q4.1 (S), Q4.2 (S), Q4.3 (S), Q6.2 (E), Q8.1 (S), Q8.2 (S), Q8.3 (S), R83.2
unnamed: D18.2 (K), D18.3 (common), Q6.1 (B), R85.1
unnamed: D19.1 (A), Q5.1 (S), Q5.2 (S), Q5.3 (S), Q7.2 (E), Q9.1 (S), Q9.2 (S), Q9.3 (S), R84.2
unnamed: D19.2 (K), D19.3 (common), Q7.1 (B), R86.1
unnamed: D20.2 (K), R116.2
unnamed: C74.1, D20.3 (common), R117.2, R120.1, TP37.1 (1_1)
unnamed: D21.1 (K), J3.3, J4.3, Q16.5 (D), TP38.1 (1_1)
unnamed: C88.1, D22.2 (K), R129.2, TP42.1 (1_1), U29.5 (V+)
unnamed: C85.1, D22.3 (common), R125.2, R128.1
unnamed: D23.3 (common), R136.2, R137.1, U31.3 (+), U31.5 (+), U32.3 (+)
unnamed: J1.1, U1.1 (GPIO0)
unnamed: J1.2, U1.2 (GPIO1)
unnamed: J5.1, R139.1, U35.1 (IO1)
unnamed: J5.3, RN9.4 (R4.1), U37.6 (IO4)
unnamed: J5.4, RN9.3 (R3.1), U37.4 (IO3)
unnamed: J5.5, RN9.2 (R2.1), U37.3 (IO2)
unnamed: J5.6, RN9.1 (R1.1), U37.1 (IO1)
unnamed: J5.7, RN8.4 (R4.1), U36.6 (IO4)
unnamed: J5.8, RN8.3 (R3.1), U36.4 (IO3)
unnamed: J5.9, RN8.2 (R2.1), U36.3 (IO2)
unnamed: J5.10, RN8.1 (R1.1), U36.1 (IO1)
unnamed: JP1.1 (A), U1.40 (VBUS)
unnamed: JP2.3 (B), R139.2
unnamed: C100.1, JP2.2 (C), TP48.1 (1_1), U38.23 (V_{CCB}), U38.24 (V_{CCB})
unnamed: L2.1, U16.8 (L1), U16.9 (L1)
unnamed: L2.2, U16.6 (L2), U16.7 (L2)
unnamed: Q1.2 (S), R53.1, TP18.1 (1_1), U16.12 (EN)
unnamed: Q2.3 (D), Q3.3 (D), R72.2, U20.4 (IN_B)
unnamed: Q10.1 (G), R92.2
unnamed: Q11.1 (G), R100.2
unnamed: Q12.1 (G), R102.2, R103.1, TP34.1 (1_1)
unnamed: Q12.2 (S), R104.1, U24.5 (S2A)
unnamed: Q13.1 (G), R105.2, R106.1, TP35.1 (1_1)
unnamed: Q13.2 (S), R107.1
unnamed: Q14.4 (G), R108.2, R109.1, TP36.1 (1_1)
unnamed: Q14.1 (S), Q14.2 (S), Q14.3 (S), R110.1
unnamed: Q15.4 (G), Q16.4 (G), R120.2
unnamed: Q15.1 (S), Q15.2 (S), Q15.3 (S), Q16.1 (S), Q16.2 (S), Q16.3 (S)
unnamed: R16.2, TP3.1 (1_1)
unnamed: R58.1, R60.1, U17.1
unnamed: R123.1, U27.2 (Rg)
unnamed: R123.2, U27.3 (Rg)
unnamed: R127.1, R129.1, U28.1
unnamed: RN1.1 (R1.1), U1.16 (GPIO12)
unnamed: RN1.2 (R2.1), RN2.2 (R2.1), U1.17 (GPIO13)
unnamed: RN1.3 (R3.1), RN2.3 (R3.1), U1.19 (GPIO14)
unnamed: RN1.4 (R4.1), RN2.4 (R4.1), U1.20 (GPIO15)
unnamed: RN3.1 (R1.1), RN4.1 (R1.1), U1.25 (GPIO19)
unnamed: RN3.2 (R2.1), RN4.2 (R2.1), U1.26 (GPIO20)
unnamed: RN3.3 (R3.1), RN4.3 (R3.1), U1.27 (GPIO21)
unnamed: RN3.4 (R4.1), RN4.4 (R4.1), U1.29 (GPIO22)
unnamed: R3.1, RN4.5 (R4.2)
unnamed: RN5.1 (R1.1), U30.8 (SCLK)
unnamed: RN5.2 (R2.1), U30.7 (DOUT)
unnamed: RN5.3 (R3.1), U30.6 (CONVST)
unnamed: RN9.8 (R1.2), RN10.1 (R1.1), U38.17 (B5)
unnamed: RN9.7 (R2.2), RN10.2 (R2.1), U38.16 (B6)
unnamed: RN9.6 (R3.2), RN10.3 (R3.1), U38.15 (B7)
unnamed: RN9.5 (R4.2), RN10.4 (R4.1), U38.14 (B8)
unnamed: RN8.8 (R1.2), RN11.1 (R1.1), U38.21 (B1)
unnamed: RN8.7 (R2.2), RN11.2 (R2.1), U38.20 (B2)
unnamed: RN8.6 (R3.2), RN11.3 (R3.1), U38.19 (B3)
unnamed: RN8.5 (R4.2), RN11.4 (R4.1), U38.18 (B4)
unnamed: R2.1, U1.33 (AGND)
unnamed: R1.2, U1.15 (GPIO11)
unnamed: R4.2, U1.34 (GPIO28_ADC2)
unnamed: SW1.2, U1.30 (RUN)
unnamed: R5.2, R6.1, U3.3 (EN/UVLO)
unnamed: R13.1, U3.7 (ILM)
unnamed: R8.1, U3.8 (OVLO/OVCSEL)
unnamed: R9.2, R10.1, U4.3 (EN/UVLO)
unnamed: R15.1, R16.1, U4.7 (ILM)
unnamed: R12.1, U4.8 (OVLO/OVCSEL)
unnamed: C4.1, U4.2 (dV/dT)
unnamed: C8.1, R18.2, R19.1, U5.4 (PR1)
unnamed: R24.2, U6.4 (CT)
unnamed: C12.1, R21.2, R22.1, U6.5 (SENSE)
unnamed: R29.2, U9.2 (~RESET), U10.4 (EN)
unnamed: C23.2, R32.2, R33.1, U10.3 (FB)
unnamed: C19.1, U11.8 (C+)
unnamed: C19.2, U11.7 (C-)
unnamed: C22.2, U11.3 (CPOUT)
unnamed: R27.2, R28.1, U11.6 (EN)
unnamed: R34.1, R36.2, U11.5 (VFB)
unnamed: C21.1, R30.2, U11.1 (VIN)
unnamed: C24.1, U12.5 (Trim/NR)
unnamed: C20.1, R31.2, U12.2 (Vin)
unnamed: R39.2, R40.1, U13.6 (PGFB)
unnamed: C30.1, R38.1, U13.7 (SET)
unnamed: R45.2, R46.1, U14.3 (+)
unnamed: C33.1, R43.2, R44.1, U14.2 (-), U14.5 (+), U14.13 (-)
unnamed: C34.1, R47.2, R48.1, U14.6 (-)
unnamed: R42.2, U14.10 (+)
unnamed: C32.1, R41.2, R43.1, U14.9 (-)
unnamed: R49.2, R50.1, U14.12 (+)
unnamed: R54.1, U15.8 (Vout)
unnamed: C38.1, R55.2, R56.1, TP19.1 (1_1), U15.6 (Vref)
unnamed: C52.2, R63.2, TP24.1 (1_1), U16.3 (FB), U19.1
unnamed: C37.1, U16.1 (VINA), U16.13 (PS/SYNC)
unnamed: C41.1, R54.2, U17.3 (+)
unnamed: R57.1, R58.2, U17.4 (-)
unnamed: C49.1, R60.2, TP23.1 (1_1), U18.4 (SET)
unnamed: R66.1, R67.2, R68.2, U19.3 (+)
unnamed: C52.1, R63.1, R64.2, U19.4 (-)
unnamed: R75.2, U20.2 (IN_A)
unnamed: R77.1, R78.1, U20.7 (OUT_A)
unnamed: R79.1, R80.1, U20.5 (OUT_B)
unnamed: R98.2, U22.2 (IN_A)
unnamed: R96.2, U22.4 (IN_B)
unnamed: R108.1, U22.5 (OUT_B)
unnamed: R99.2, U23.2 (IN_A)
unnamed: R97.2, U23.4 (IN_B)
unnamed: R105.1, U23.7 (OUT_A)
unnamed: R102.1, U23.5 (OUT_B)
unnamed: R112.2, U24.1 (A0)
unnamed: R111.2, U24.16 (A1)
unnamed: R113.2, U24.2 (EN)
unnamed: R107.2, U24.6 (S3A)
unnamed: R107.3, U24.11 (S3B)
unnamed: R110.2, U24.7 (S4A)
unnamed: R110.3, U24.10 (S4B)
unnamed: R114.2, U25.3 (+)
unnamed: R118.1, R119.1, U25.1, U25.4 (-)
unnamed: C78.1, R121.2, R122.1, U26.3 (+)
unnamed: TP41.1 (1_1), U26.1, U26.4 (-), U27.6 (Ref)
unnamed: R126.2, U28.3 (+)
unnamed: R124.1, R127.2, U28.4 (-)
unnamed: C87.1, R128.2, U29.3 (+)
unnamed: C85.2, R130.1, U29.1, U29.4 (-)
unnamed: C90.1, R130.2, TP43.1 (1_1), U30.3 (AINP)
unnamed: C93.1, R132.2, R133.1, U31.2 (-)
unnamed: C94.1, R133.2, R134.1, U31.6 (-)
unnamed: C95.1, R134.2, R135.1, U32.4 (-)
unnamed: U33.9 (Q7), U34.10 (DS)
unnamed: R138.1, U34.9 (Q7)
unnamed: R146.1, U39.2 (V_{OUT})
unnamed: C103.1, R140.2, R149.1, U40.1 (CH0)
unnamed: C104.1, R141.2, R150.1, U40.2 (CH1)
unnamed: C105.1, R142.2, R143.1, R151.1, U40.3 (CH2)
unnamed: C106.1, R144.2, U40.4 (CH3)
unnamed: C107.1, R145.2, U40.5 (CH4)
unnamed: C108.1, R146.2, U40.6 (CH5)
unnamed: C109.1, R147.2, R152.1, U40.7 (CH6)
unnamed: C110.1, R148.2, R153.1, U40.8 (CH7)
VREF: C113.1, D7.2 (A), R35.1, R49.1, R55.1, R68.1, R121.1, R126.1, R131.1, R132.1, R148.1, TP14.1 (1_1), U12.6 (Vout), U21.4 (-), U30.1 (REF), U40.15 (Vref)

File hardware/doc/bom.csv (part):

"Reference","Value","Footprint","MPN","Manufacturer","QUANTITY"
"C1,C3,C13,C25,C35-C38,C44,C48,C49,C51,C54,C55,C57,C59-C61,C66-C70,C72,C73,C79-C81,C84,C86,C88,C93-C111,C113","100n 50V X7R","Capacitor_SMD:C_0603_1608Metric","C0603C104K5RACTU","KEMET","51"
"C2,C18,C20,C22,C28,C30,C63","4.7u 25V X7R","Capacitor_SMD:C_0805_2012Metric","CL21B475KAFNNNE","Samsung Electro-Mechanics","7"
"C4","3.3n 50V X7R","Capacitor_SMD:C_0603_1608Metric","CL10B332KB8NNNC","Samsung Electro-Mechanics","1"
"C5,C39,C40,C46","10u 25V X5R","Capacitor_SMD:C_0805_2012Metric","CL21A106KAYNNNE","Samsung Electro-Mechanics","4"
"C6,C7,C14-C17,C19,C24,C41,C47,C56,C62,C64,C65,C78,C82,C83,C91,C92,C112","1u 25V X7R","Capacitor_SMD:C_0603_1608Metric","C0603C105K3RACTU","KEMET","20"
"C8","33n 50V X7R","Capacitor_SMD:C_0603_1608Metric","CL10B333KB8NNNC","Samsung Electro-Mechanics","1"
"C9,C10,C21","22u 10V X7R","Capacitor_SMD:C_1206_3216Metric","CL31B226KPHNNNE","Samsung Electro-Mechanics","3"
"C11","47u 16V","Capacitor_SMD:CP_Elec_6.3x5.4","865060343004","Wurth Elektronik","1"
"C12,C58","1n 50V C0G","Capacitor_SMD:C_0603_1608Metric","C0603C102J5GACTU","KEMET","2"
"C23,C77","220p 50V C0G","Capacitor_SMD:C_0603_1608Metric","C0603C221J5GACTU","KEMET","2"
"C26","10u 16V X7R","Capacitor_SMD:C_0805_2012Metric","CL21B106KOQNNNE","Samsung Electro-Mechanics","1"
"C27,C29,C31","10u 25V X7R","Capacitor_SMD:C_1210_3225Metric","CL32B106KAJNNNE","Samsung Electro-Mechanics","3"
"C32-C34,C74","10n 50V C0G","Capacitor_SMD:C_0603_1608Metric","GRM1885C1H103JA01D","Murata","4"
"C42,C43,C45,C50,C53","22u 25V X5R","Capacitor_SMD:C_1206_3216Metric","CL31A226KAHNNNE","Samsung Electro-Mechanics","5"
"C52","10p 50V C0G","Capacitor_SMD:C_0603_1608Metric","C0603C100J5GACTU","KEMET","1"
"C71","100n 50V C0G","Capacitor_SMD:C_1206_3216Metric","C3216C0G1H104J160AA","TDK","1"
"C75,C76","22p 50V C0G","Capacitor_SMD:C_0603_1608Metric","C0603C220J5GACTU","KEMET","2"
"C85","1.5n 50V C0G","Capacitor_SMD:C_0603_1608Metric","C0603C152J5GACTU","KEMET","1"
"C87","680p 50V C0G","Capacitor_SMD:C_0603_1608Metric","C0603C681J5GACTU","KEMET","1"
"C89","22u 6.3V X5R","Capacitor_SMD:C_0805_2012Metric","CL21A226KQQNNNE","Samsung Electro-Mechanics","1"
"C90","10n 25V C0G","Capacitor_SMD:C_0603_1608Metric","C0603C103J3GACTU","KEMET","1"
"D1,D3,D4,D11,D12","1N5819HW","Diode_SMD:D_SOD-123","1N5819HW-7-F","Diodes Incorporated","5"
"D2","SMAJ10A","Diode_SMD:D_SMA","SMAJ10A-E3/61","Vishay","1"
"D5","green 2.0V","LED_SMD:LED_0603_1608Metric","150060VS75000","Wurth Elektronik","1"
"D6-D9","B0530W 30V 0.5A","Diode_SMD:D_SOD-123","B0530W-7-F","Diodes Incorporated","4"
"D10,D13,D15-D20,D22,D23","BAV199","Package_TO_SOT_SMD:SOT-23","BAV199-7-F","Diodes Incorporated","10"
"D14","SMAJ20CA","Diode_SMD:D_SMA","SMAJ20CA-E3/61","Vishay","1"
"D21","PTVS15VS1UR","Diode_SMD:Nexperia_CFP3_SOD-123W","PTVS15VS1UR,115","Nexperia","1"
"D24","BAT54S","Package_TO_SOT_SMD:SOT-23","BAT54SLT1G","onsemi","1"
"F1","4A fast 32V","Fuse:Fuse_1206_3216Metric","0466004.NR","Littelfuse","1"
"FB1","50R 12A","Inductor_SMD:L_1206_3216Metric","BLM31SN500SN1L","Murata","1"
"J1","Debug UART","Connector_PinHeader_2.54mm:PinHeader_1x03_P2.54mm_Vertical","61300311121","Wurth Elektronik","1"
"J2","USB-C power","Connector_USB:USB_C_Receptacle_GCT_USB4125-xx-x_6P_TopMnt_Horizontal","USB4125-GF-A-0190","GCT","1"
"J3","DUT","Connector_PinHeader_2.54mm:PinHeader_1x04_P2.54mm_Vertical","61300411121","Wurth Elektronik","1"
"J4","DUT wires","PowerProfiler:TerminalBlock_WAGO_2601-1104_1x04_P3.50mm_Horizontal_Pad1.9mm","2601-1104","WAGO","1"
"J5","Logic port","Connector_PinHeader_2.54mm:PinHeader_1x10_P2.54mm_Vertical","61301011121","Wurth Elektronik","1"
"L1","10u 3A","Inductor_SMD:L_Wuerth_MAPI-4030","74438357100","Wurth Elektronik","1"
"L2","1.5u 4.6A","Inductor_SMD:L_Coilcraft_XxL4020","XFL4020-152MEC","Coilcraft","1"
"MP1,MP2","Socket 1x20 2.54 mm","","61302011821","Wurth Elektronik","2"
"MP3","BMI-S-210-C","","BMI-S-210-C","Laird","1"
"Q1-Q3","BSS138","Package_TO_SOT_SMD:SOT-23","BSS138-7-F","Diodes Incorporated","3"
"Q4,Q5,Q8,Q9,Q14-Q16","CSD17577Q3A","Package_SON:VSON-8_3.3x3.3mm_P0.65mm_NexFET","CSD17577Q3A","Texas Instruments","7"
"Q6,Q7","BC847B","Package_TO_SOT_SMD:SOT-23","BC847B-7-F","Diodes Incorporated","2"
"Q10-Q13","IRLML0030","Package_TO_SOT_SMD:SOT-23","IRLML0030TRPBF","Infineon","4"
"R1,R71","4.7k 1%","Resistor_SMD:R_0603_1608Metric","CRCW06034K70FKEA","Vishay","2"
"R2","0R","Resistor_SMD:R_0603_1608Metric","CRCW06030000Z0EA","Vishay","1"
"R3,R51","1.5k 1%","Resistor_SMD:R_0603_1608Metric","CRCW06031K50FKEA","Vishay","2"
"R4,R26,R53,R60,R62,R70,R72,R75,R88,R89,R93,R94,R96-R99,R111,R112,R118,R146","1k 1%","Resistor_SMD:R_0603_1608Metric","CRCW06031K00FKEA","Vishay","20"
"R5,R9","4.53k 1%","Resistor_SMD:R_0603_1608Metric","CRCW06034K53FKEA","Vishay","2"
"R6,R10","3.01k 1%","Resistor_SMD:R_0603_1608Metric","CRCW06033K01FKEA","Vishay","2"
"R7,R11,R91,R95","5.1k 1%","Resistor_SMD:R_0603_1608Metric","CRCW06035K10FKEA","Vishay","4"
"R8,R12","402k 1%","Resistor_SMD:R_0603_1608Metric","CRCW0603402KFKEA","Vishay","2"
"R13","1.21k 1%","Resistor_SMD:R_0603_1608Metric","CRCW06031K21FKEA","Vishay","1"
"R14,R20,R59","0.33R 1%","Resistor_SMD:R_0805_2012Metric","ERJ-6RQFR33V","Panasonic","3"
"R15","453R 1%","Resistor_SMD:R_0603_1608Metric","CRCW0603453RFKEA","Vishay","1"
"R16,R19,R23,R25,R41,R54,R113,R114,R126,R144,R145,R150,R152","10k 1%","Resistor_SMD:R_0603_1608Metric","CRCW060310K0FKEA","Vishay","13"
"R17,R24,R27,R42,R50,R78,R80,R85,R86,R90,R103,R106,R109,R115,R148,R149,R151","100k 1%","Resistor_SMD:R_0603_1608Metric","CRCW0603100KFKEA","Vishay","17"
"R18","13.7k 1%","Resistor_SMD:R_0603_1608Metric","CRCW060313K7FKEA","Vishay","1"
"R21","86.6k 0.1%","Resistor_SMD:R_0603_1608Metric","TNPW060386K6BEEA","Vishay","1"
"R22,R57","10k 0.1% 25ppm","Resistor_SMD:R_0603_1608Metric","TNPW060310K0BEEA","Vishay","2"
"R28","150k 1%","Resistor_SMD:R_0603_1608Metric","CRCW0603150KFKEA","Vishay","1"
"R29","51k 1%","Resistor_SMD:R_0603_1608Metric","CRCW060351K0FKEA","Vishay","1"
"R30","2.2R 1% 0.25W","Resistor_SMD:R_1206_3216Metric","CRCW12062R20FKEA","Vishay","1"
"R31,R61,R108,R120,R129","10R 1%","Resistor_SMD:R_0603_1608Metric","CRCW060310R0FKEA","Vishay","5"
"R32","133k 1%","Resistor_SMD:R_0603_1608Metric","CRCW0603133KFKEA","Vishay","1"
"R33","13.3k 1%","Resistor_SMD:R_0603_1608Metric","CRCW060313K3FKEA","Vishay","1"
"R34","226k 0.1%","Resistor_SMD:R_0603_1608Metric","TNPW0603226KBEEA","Vishay","1"
"R35","1R 1%","Resistor_SMD:R_0603_1608Metric","CRCW06031R00FNEA","Vishay","1"
"R36,R67,R74","100k 0.1% 25ppm","Resistor_SMD:R_0603_1608Metric","TNPW0603100KBEEA","Vishay","3"
"R37","0.47R 1% 0.25W","Resistor_SMD:R_1206_3216Metric","ERJ-8RQFR47V","Panasonic","1"
"R38","120k 0.1%","Resistor_SMD:R_0603_1608Metric","TNPW0603120KBEEA","Vishay","1"
"R39","442k 1%","Resistor_SMD:R_0603_1608Metric","CRCW0603442KFKEA","Vishay","1"
"R40","12.4k 1%","Resistor_SMD:R_0603_1608Metric","CRCW060312K4FKEA","Vishay","1"
"R43","40.2k 1%","Resistor_SMD:R_0603_1608Metric","CRCW060340K2FKEA","Vishay","1"
"R44,R46,R47","49.9k 1%","Resistor_SMD:R_0603_1608Metric","CRCW060349K9FKEA","Vishay","3"
"R45","249k 1%","Resistor_SMD:R_0603_1608Metric","CRCW0603249KFKEA","Vishay","1"
"R48","127k 1%","Resistor_SMD:R_0603_1608Metric","CRCW0603127KFKEA","Vishay","1"
"R49","36.5k 1%","Resistor_SMD:R_0603_1608Metric","CRCW060336K5FKEA","Vishay","1"
"R52,R81,R82","6.8k 1%","Resistor_SMD:R_0603_1608Metric","CRCW06036K80FKEA","Vishay","3"
"R55,R56","2.00k 0.1% 25ppm","Resistor_SMD:R_0603_1608Metric","TNPW06032K00BEEA","Vishay","2"
"R58,R124","11k 0.1% 25ppm","Resistor_SMD:R_0603_1608Metric","TNPW060311K0BEEA","Vishay","2"
"R63","19.1k 0.1% 25ppm","Resistor_SMD:R_0603_1608Metric","TNPW060319K1BEEA","Vishay","1"
"R64","93.1k 0.1% 25ppm","Resistor_SMD:R_0603_1608Metric","TNPW060393K1BEEA","Vishay","1"
"R65","6.65k 0.1% 25ppm","Resistor_SMD:R_0603_1608Metric","TNPW06036K65BEEA","Vishay","1"
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

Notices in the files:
README.md:
License:
- Hardware design files under [`hardware/`](hardware/):
[CERN-OHL-P v2](hardware/LICENSE).
- What derives from those files in [`simulation/`](simulation/README.md#license):
the snapshot of the netlist in `simulation/netlist/` and the decks,
records, graphs and pages in `simulation/results/`, under the same
CERN-OHL-P v2, with a copy of the license in each of the two folders.
- Everything else, including firmware, host software, tools, the
simulation package with its benches and models, and documentation:
[MIT](LICENSE).
